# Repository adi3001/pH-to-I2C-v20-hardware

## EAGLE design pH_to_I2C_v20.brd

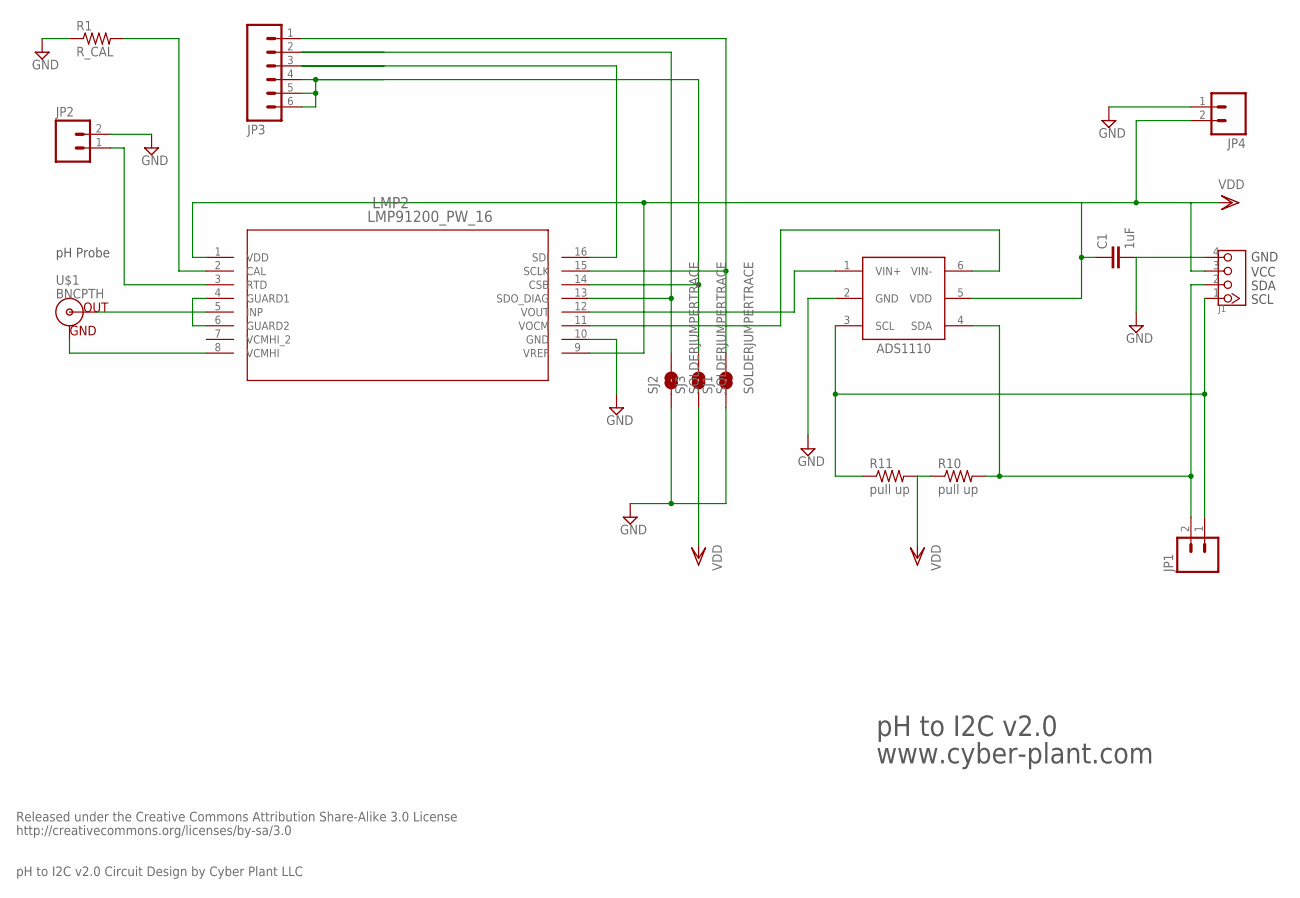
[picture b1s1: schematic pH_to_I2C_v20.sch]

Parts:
C1: 1uF; 1206
IC1: ADS1110; SOT-23-6
J1: TWIG-4P-2.090D; 4P-2.0-90D
JP1, JP2, JP4: M02PTH; 1X02
JP3: M06SIP; 1X06
LMP2: LMP91200_PW_16; MTC16
R1: R_CAL; AXIAL-0.4
R10, R11: pull up; AXIAL-0.4
SJ1, SJ2, SJ3: SOLDERJUMPERTRACE; SJ_2S-TRACE
U$1: BNCPTH; BNC

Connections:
GND: C1.2, IC1.2 (GND), J1.4, JP2.2, JP4.1, LMP2.10 (GND), R1.P$1 (1), SJ1.1, SJ2.1
unnamed: JP3.1, LMP2.15 (SCLK), SJ1.2
unnamed: JP3.2, LMP2.13 (SDO_DIAG), SJ2.2
unnamed: IC1.4 (SDA), J1.2, JP1.2, R10.P$2 (2)
unnamed: IC1.1 (VIN+), LMP2.12 (VOUT)
unnamed: IC1.6 (VIN-), LMP2.11 (VOCM)
unnamed: IC1.3 (SCL), J1.1, JP1.1, R11.P$1 (1)
unnamed: JP3.4, JP3.5, JP3.6, LMP2.14 (CSB), SJ3.2
unnamed: JP2.1, LMP2.3 (RTD)
unnamed: LMP2.8 (VCMHI), U$1.GND
unnamed: LMP2.5 (INP), U$1.S (OUT)
unnamed: LMP2.2 (CAL), R1.P$2 (2)
unnamed: LMP2.4 (GUARD1), LMP2.6 (GUARD2)
unnamed: JP3.3, LMP2.16 (SDI)
VDD: C1.1, IC1.5 (VDD), J1.3, JP4.2, LMP2.1 (VDD), LMP2.9 (VREF), R10.P$1 (1), R11.P$2 (2), SJ3.1

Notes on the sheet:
pH Probe
GND
VCC
SDA
SCL
pH to I2C v2.0
www.cyber-plant.com
Released under the Creative Commons Attribution Share-Alike 3.0 License
http://creativecommons.org/licenses/by-sa/3.0
pH to I2C v2.0 Circuit Design by Cyber Plant LLC

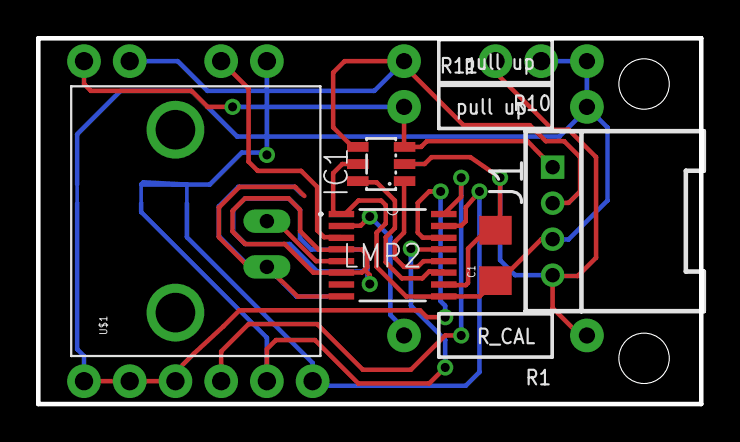
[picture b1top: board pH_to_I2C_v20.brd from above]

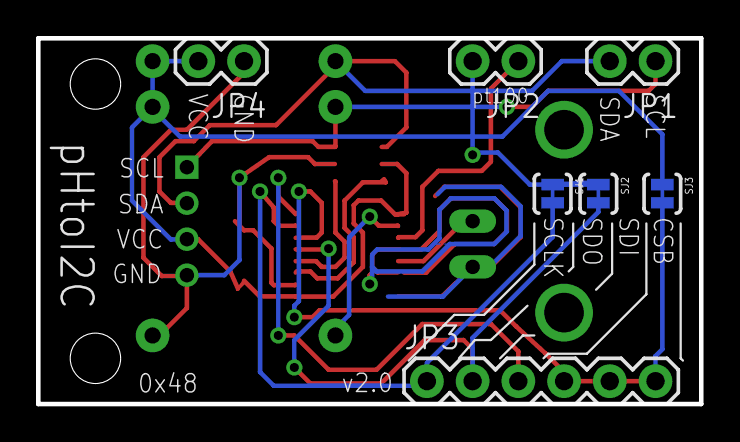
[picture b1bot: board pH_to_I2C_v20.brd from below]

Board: 2 copper layers, 36.8 x 20.3 mm, 15 parts (7 on the bottom side), 15 nets.

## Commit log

2015-11-14 :octocat: Added .gitattributes & .gitignore files
2015-11-14 hardware
    v2.0
